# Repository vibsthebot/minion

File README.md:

# Minion - The Swiss Army Knife of Electronics

I'm a mac user, and i love my apple wired headphones.
mN phone doesn't have headphone jack and my computer doesn't have micro sd or usb a.
What if i made a dongle to rule all dongles, but added a potentiometer for step tracking and display + buttons to play games? And thats how I made Minion.

## Features

- USB hub with usb c input, usb a and microsd output
- TRRS jack for headphones
- Bourns Rotary Encoder
- Built-in display (SSD1351)
- Tactile buttons for user input
- Robust case design with custom rotary encoder cover and button extensions

## [Onshape](https://cad.onshape.com/documents/3528835cd7c24f4fa682b200/w/cef528dd0bdfad9cc29e4192/e/ba726118fc6deb21c1d0aa06?renderMode=0&uiState=683c8a64ca486b08201f4fa6)

## Images

### Schematic

### PCB Layout

### 3D Model of PCB

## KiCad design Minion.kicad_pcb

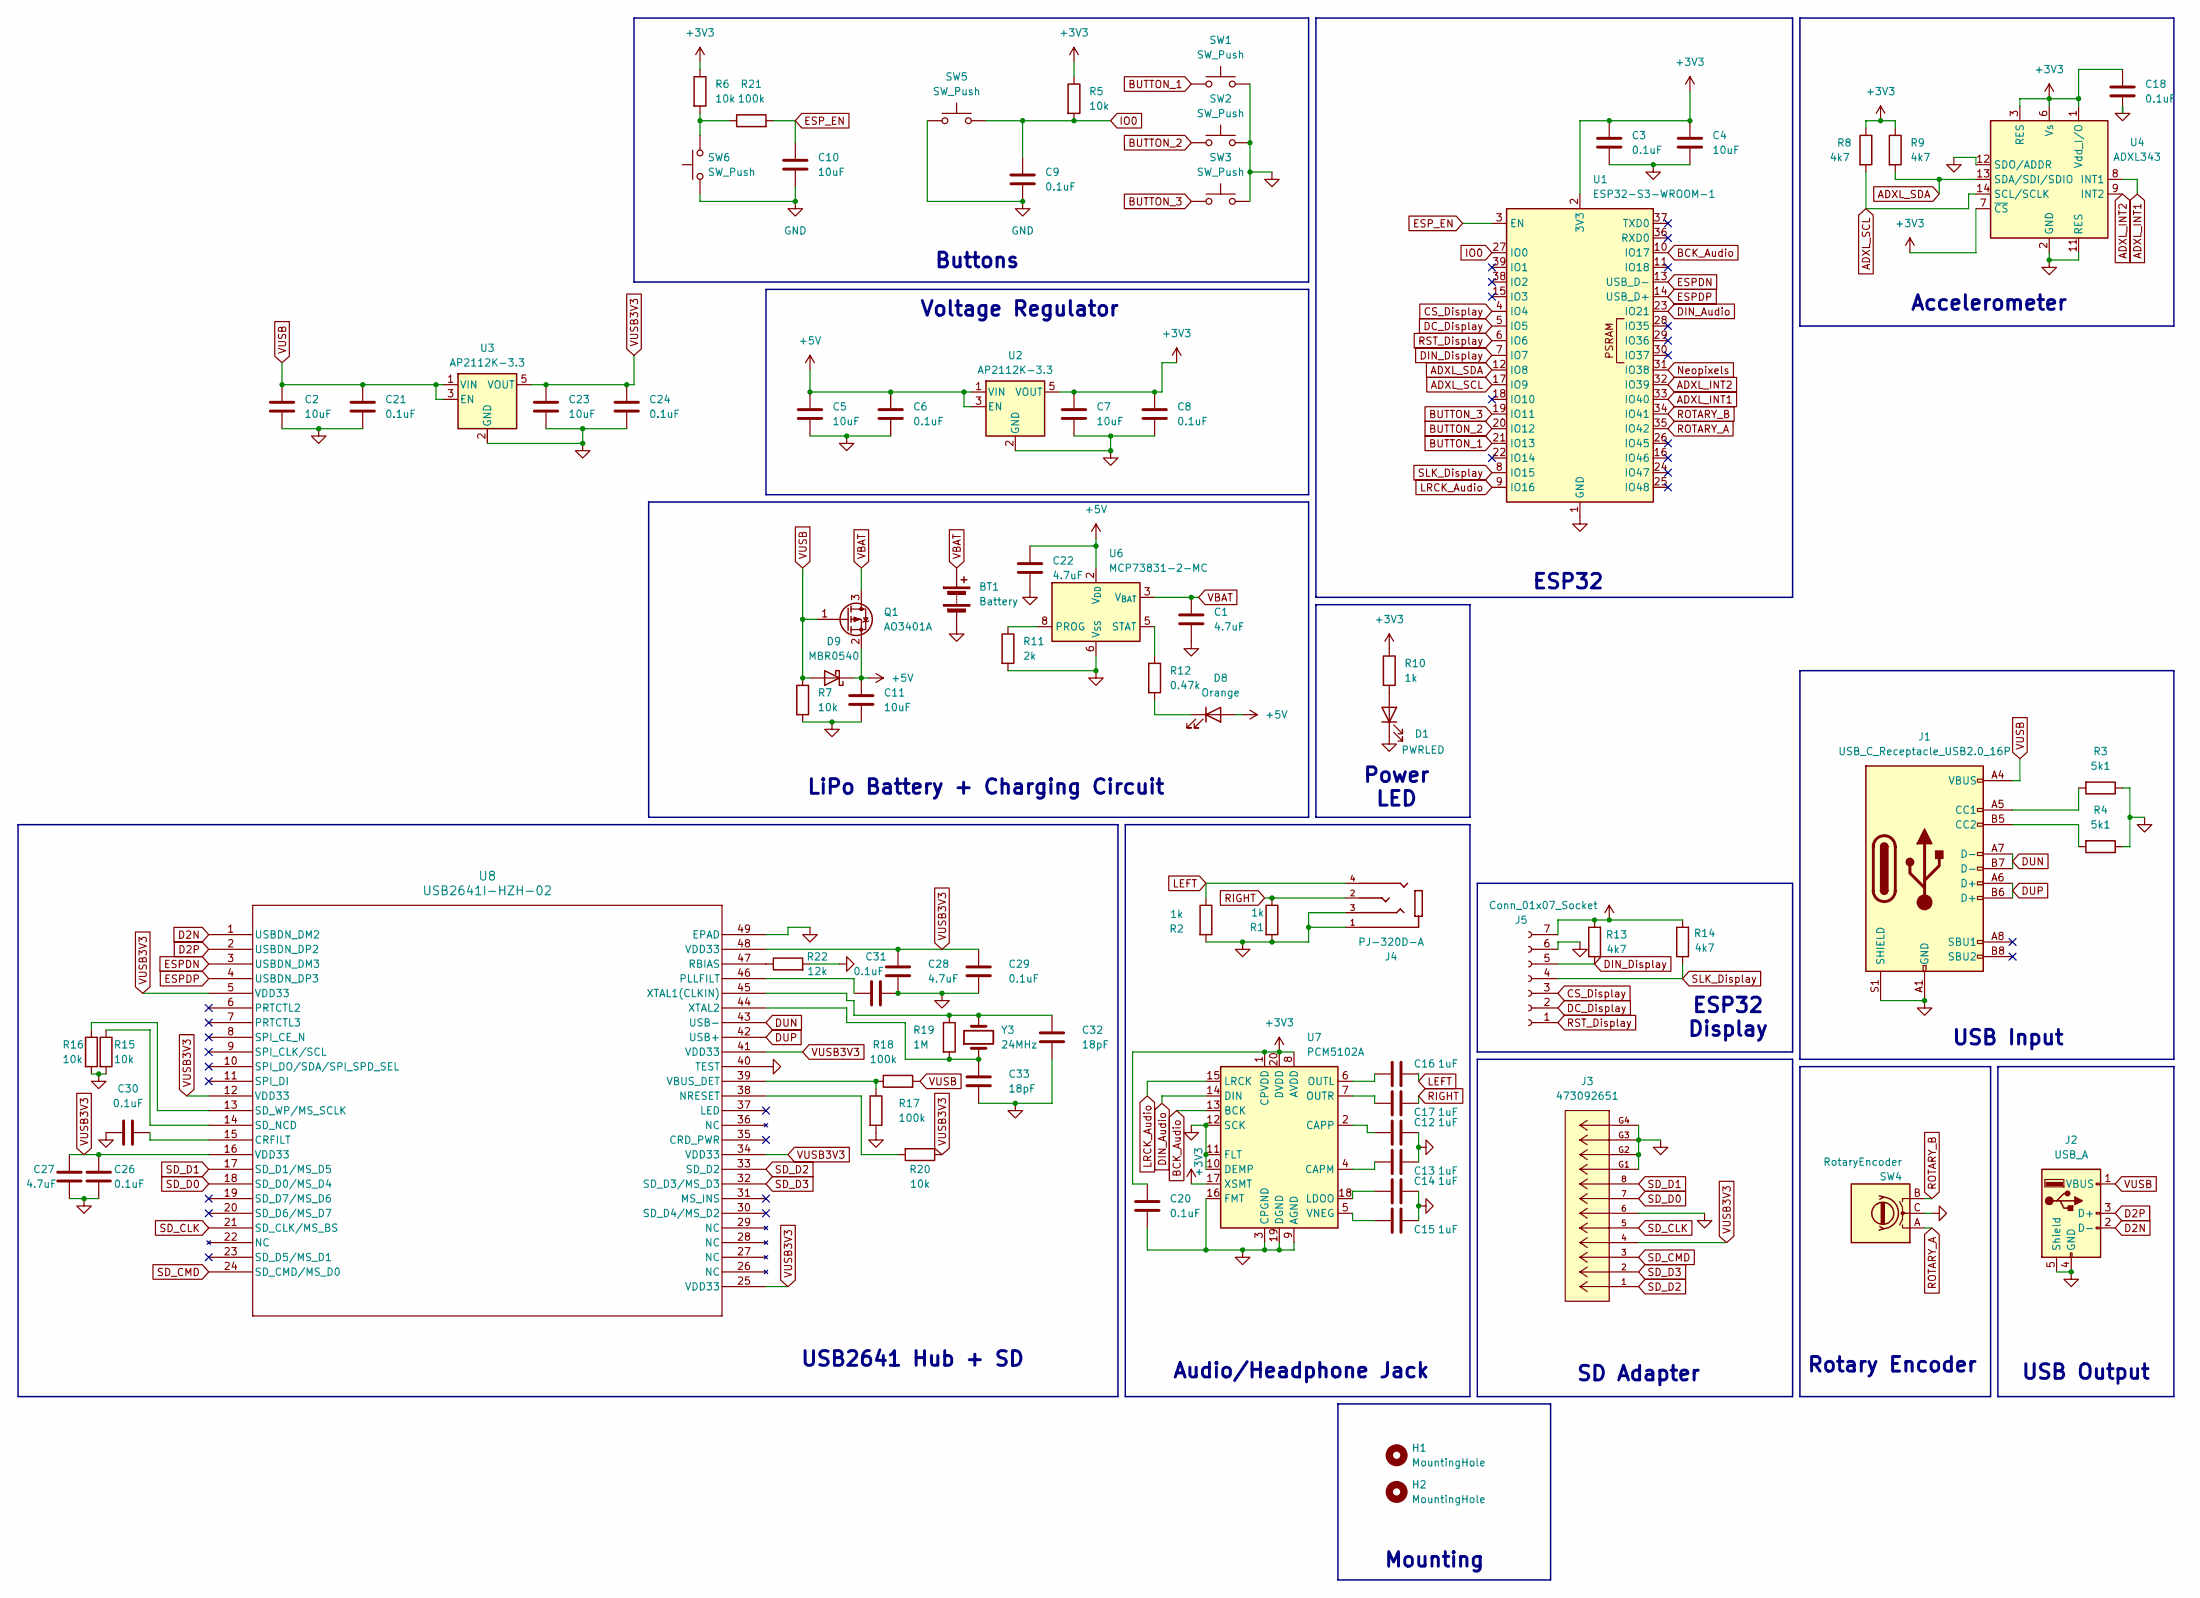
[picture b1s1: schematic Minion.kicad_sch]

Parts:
BT1: Battery; JST_PH_S2B-PH-K_1x02_P2.00mm_Horizontal; LCSC C265016
C1, C22, C27, C28: 4.7uF; C_0805_2012Metric; LCSC C1779
C2, C4, C5, C7, C10, C11, C23: 10uF; C_0805_2012Metric; LCSC C15850
C3, C6, C8, C9, C18, C20, C21, C24, C26, C29, C30, C31: 0.1uF; C_0805_2012Metric; LCSC C28233
C12, C13, C14, C15, C16, C17: 1uF; C_0805_2012Metric; LCSC C28323
C32, C33: 18pF; C_0402_1005Metric; LCSC C1549
D1: PWRLED; LED_0805_2012Metric; LCSC C84256
D8: Orange; LED_0805_2012Metric; LCSC C434437
D9: MBR0540; D_SOD-123; LCSC C77337
H1, H2: MountingHole; MountingHole_2.2mm_M2
J1: USB_C_Receptacle_USB2.0_16P; USB_C_Receptacle_HCTL_HC-TYPE-C-16P-01A; DigiKey 900-2171790001CT-ND
J2: USB_A; USB_A_Molex_67643_Horizontal; LCSC C464564
J3: 473092651; CONN12_47309-2651_MOL; MANUFACTURER_PART_NUMBER 473092651; DigiKey WM6700CT-ND
J4: PJ-320D-A; HRO_PJ-320D-A; PARTREV B; LCSC C95562
J5: Conn_01x07_Socket; SSD_1351; LCSC C124418
Q1: AO3401A; SOT-23; LCSC C306862
R1, R2, R10: 1k; R_0805_2012Metric; LCSC C17513
R3, R4: 5k1; R_0805_2012Metric; LCSC C27834
R5, R6, R7, R15, R16, R20: 10k; R_0805_2012Metric; LCSC C17414
R8, R9, R13, R14: 4k7; R_0805_2012Metric; LCSC C17673
R11: 2k; R_0805_2012Metric; LCSC C17604
R12: 0.47k; R_0805_2012Metric; LCSC C17710
R17, R18, R21: 100k; R_0805_2012Metric; LCSC C149504
R19: 1M; R_0805_2012Metric; LCSC C17514
R22: 12k; R_0805_2012Metric; LCSC C17444
SW1, SW2, SW3: SW_Push; SW_Push_1P1T_NO_6x6mm_H9.5mm; LCSC C455110
SW4: RotaryEncoder; RotaryEncoder_Bourns_Vertical_PEC12R-3x17F-Nxxxx; LCSC C18164805
SW5, SW6: SW_Push; SW_Push_1P1T_NO_CK_KMR2; LCSC C221676
U1: ESP32-S3-WROOM-1; LCSC C2913204
U2, U3: AP2112K-3.3; SOT-23-5; LCSC C51118
U4: ADXL343; LGA-14_3x5mm_P0.8mm_LayoutBorder1x6y; DigiKey 505-ADXL343BCCZ-ND
U6: MCP73831-2-MC; DFN-8-1EP_3x2mm_P0.5mm_EP1.7x1.4mm; LCSC C150772
U7: PCM5102A; TSSOP-20_4.4x6.5mm_P0.65mm; DigiKey 296-36707-1-ND
U8: USB2641I-HZH-02; QFN48_7X7MC_MCH; LCSC C633597
Y3: 24MHz; Crystal_SMD_5032-2Pin_5.0x3.2mm; LCSC C122520

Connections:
+3V3: C3.1, C4.1, C7.1, C8.1, C18.1, C20.1, J5.7, R5.1, R6.1, R8.1, R9.1, R10.1, R13.2, R14.2, U1.2 (3V3), U2.5 (VOUT), U4.1 (Vdd_I/O), U4.3 (RES), U4.6 (Vs), U4.7 (~CS), U7.1 (CPVDD), U7.8 (AVDD), U7.17 (XSMT), U7.20 (DVDD)
+5V: C5.1, C6.1, C11.1, C22.1, D8.2 (A), D9.1 (K), Q1.2 (S), U2.1 (VIN), U2.3 (EN), U6.1 (V_{DD}), U6.2 (V_{DD})
ADXL_INT1: U1.33 (IO40), U4.8 (INT1)
ADXL_INT2: U1.32 (IO39), U4.9 (INT2)
ADXL_SCL: R8.2, U1.17 (IO9), U4.14 (SCL/SCLK)
ADXL_SDA: R9.2, U1.12 (IO8), U4.13 (SDA/SDI/SDIO)
BCK_Audio: U1.10 (IO17), U7.13 (BCK)
BUTTON_1: SW1.1, U1.21 (IO13)
BUTTON_2: SW2.1, U1.20 (IO12)
BUTTON_3: SW3.1, U1.19 (IO11)
CS_Display: J5.3, U1.4 (IO4)
D2N: J2.2 (D-), U8.1 (USBDN_DM2)
D2P: J2.3 (D+), U8.2 (USBDN_DP2)
DC_Display: J5.2, U1.5 (IO5)
DIN_Audio: U1.23 (IO21), U7.14 (DIN)
DIN_Display: J5.5, R13.1, U1.7 (IO7)
DUN: J1.A7 (D-), J1.B7 (D-), U8.43 (USB-)
DUP: J1.A6 (D+), J1.B6 (D+), U8.42 (USB+)
ESPDN: U1.13 (USB_D-), U8.3 (USBDN_DM3)
ESPDP: U1.14 (USB_D+), U8.4 (USBDN_DP3)
ESP_EN: C10.1, R21.2, U1.3 (EN)
GND: BT1.2 (-), C1.2, C2.2, C3.2, C4.2, C5.2, C6.2, C7.2, C8.2, C9.2, C10.2, C11.2, C12.2, C13.2, C14.2, C15.2, C18.2, C20.2, C21.2, C22.2, C23.2, C24.2, C26.2, C27.2, C28.2, C29.2, C30.1, C31.2, C32.2, C33.2, D1.1 (K), J1.A1 (GND), J1.A12 (GND), J1.B1 (GND), J1.B12 (GND), J1.S1 (SHIELD), J2.4 (GND), J2.5 (Shield), J3.6, J3.G1, J3.G2, J3.G3, J3.G4, J4.1, J4.3, J5.6, R1.2, R2.2, R3.1, R4.1, R7.2, R11.2, R15.2, R16.2, R17.2, R22.2, SW1.2, SW2.2, SW3.2, SW4.C, SW5.1, SW6.1, U1.1 (GND), U1.40 (GND), U1.41 (GND), U2.2 (GND), U3.2 (GND), U4.2 (GND), U4.4 (GND), U4.5 (GND), U4.11 (RES), U4.12 (SDO/ADDR), U6.6 (V_{SS}), U7.3 (CPGND), U7.9 (AGND), U7.10 (DEMP), U7.11 (FLT), U7.12 (SCK), U7.16 (FMT), U7.19 (DGND), U8.40 (TEST), U8.49 (EPAD)
IO0: C9.1, R5.2, SW5.2, U1.27 (IO0)
LEFT: C16.2, J4.4, R2.1
LRCK_Audio: U1.9 (IO16), U7.15 (LRCK)
Neopixels: U1.31 (IO38)
unnamed: D1.2 (A), R10.2
unnamed: D8.1 (K), R12.2
unnamed: J1.A5 (CC1), R3.2
unnamed: J1.B5 (CC2), R4.2
unnamed: R6.2, R21.1, SW6.2
unnamed: R11.1, U6.8 (PROG)
unnamed: R12.1, U6.5 (STAT)
unnamed: C13.1, U7.4 (CAPM)
unnamed: C12.1, U7.2 (CAPP)
unnamed: C14.1, U7.18 (LDOO)
unnamed: C16.1, U7.6 (OUTL)
unnamed: C17.1, U7.7 (OUTR)
unnamed: C15.1, U7.5 (VNEG)
unnamed: C30.2, U8.15 (CRFILT)
unnamed: R20.2, U8.38 (NRESET)
unnamed: C31.1, U8.46 (PLLFILT)
unnamed: R22.1, U8.47 (RBIAS)
unnamed: R15.1, U8.14 (SD_NCD)
unnamed: R16.1, U8.13 (SD_WP/MS_SCLK)
unnamed: R17.1, R18.1, U8.39 (VBUS_DET)
unnamed: C32.1, R19.1, U8.45 (XTAL1(CLKIN)), Y3.2
unnamed: C33.1, R19.2, U8.44 (XTAL2), Y3.1
RIGHT: C17.2, J4.2, R1.1
ROTARY_A: SW4.A, U1.35 (IO42)
ROTARY_B: SW4.B, U1.34 (IO41)
RST_Display: J5.1, U1.6 (IO6)
SD_CLK: J3.5, U8.21 (SD_CLK/MS_BS)
SD_CMD: J3.3, U8.24 (SD_CMD/MS_D0)
SD_D0: J3.7, U8.18 (SD_D0/MS_D4)
SD_D1: J3.8, U8.17 (SD_D1/MS_D5)
SD_D2: J3.1, U8.33 (SD_D2)
SD_D3: J3.2, U8.32 (SD_D3/MS_D3)
SLK_Display: J5.4, R14.1, U1.8 (IO15)
VBAT: BT1.1 (+), C1.1, Q1.3 (D), U6.3 (V_{BAT}), U6.4 (V_{BAT})
VUSB: C2.1, C21.1, D9.2 (A), J1.A4 (VBUS), J1.A9 (VBUS), J1.B4 (VBUS), J1.B9 (VBUS), J2.1 (VBUS), Q1.1 (G), R7.1, R18.2, U3.1 (VIN), U3.3 (EN)
VUSB3V3: C23.1, C24.1, C26.1, C27.1, C28.1, C29.1, J3.4, R20.1, U3.5 (VOUT), U8.5 (VDD33), U8.12 (VDD33), U8.16 (VDD33), U8.25 (VDD33), U8.34 (VDD33), U8.41 (VDD33), U8.48 (VDD33)

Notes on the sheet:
Voltage Regulator
Buttons
Audio/Headphone Jack
ESP32
Power LED
Mounting
USB2641 Hub + SD
Accelerometer
LiPo Battery + Charging Circuit
USB Input
USB Output
Rotary Encoder
SD Adapter
ESP32 Display

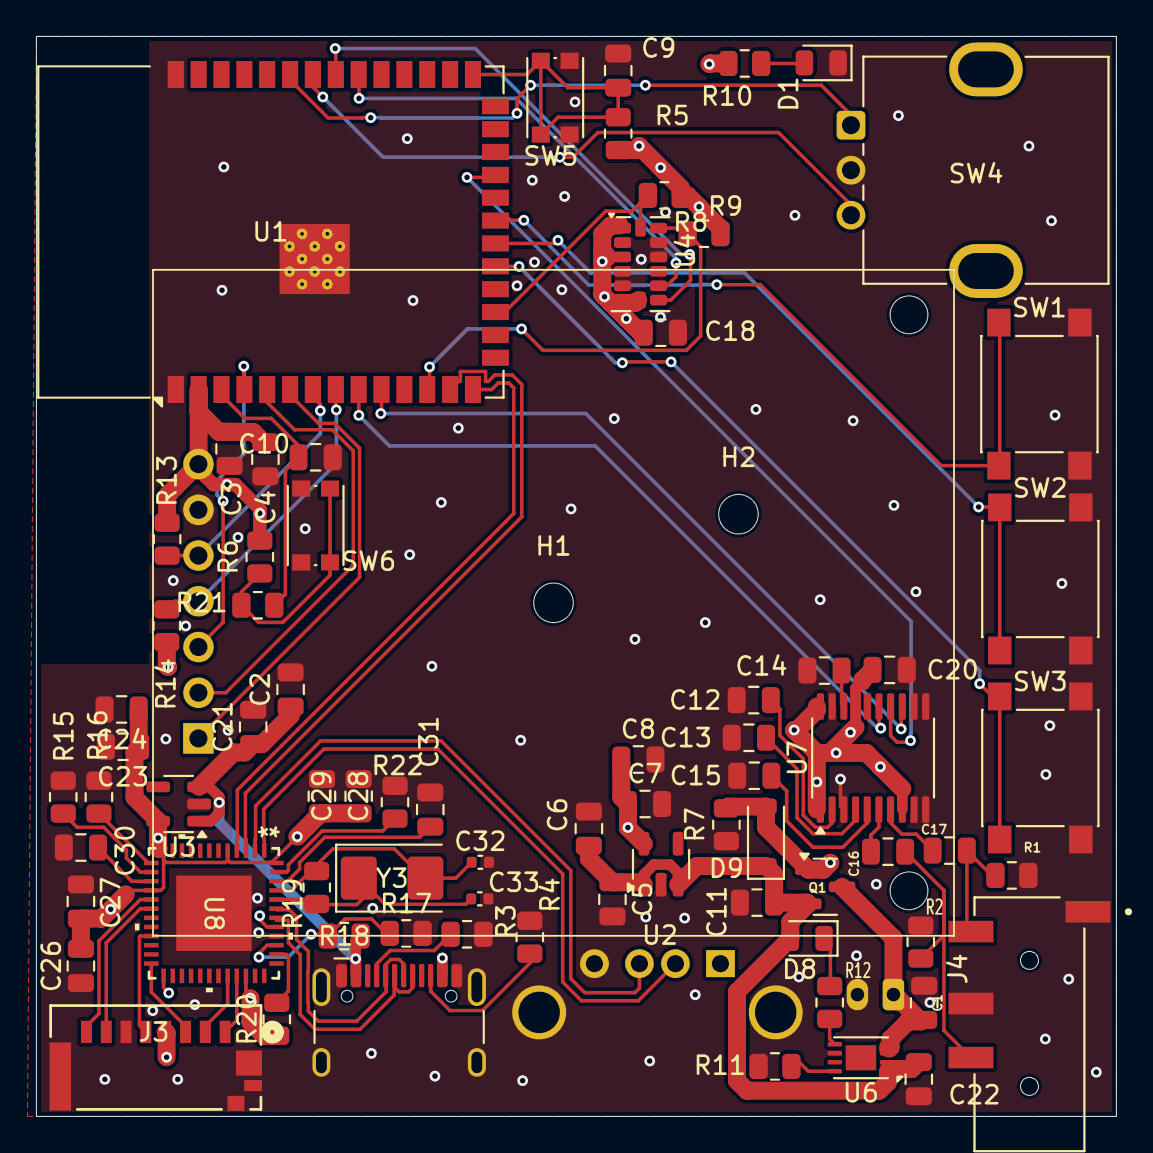
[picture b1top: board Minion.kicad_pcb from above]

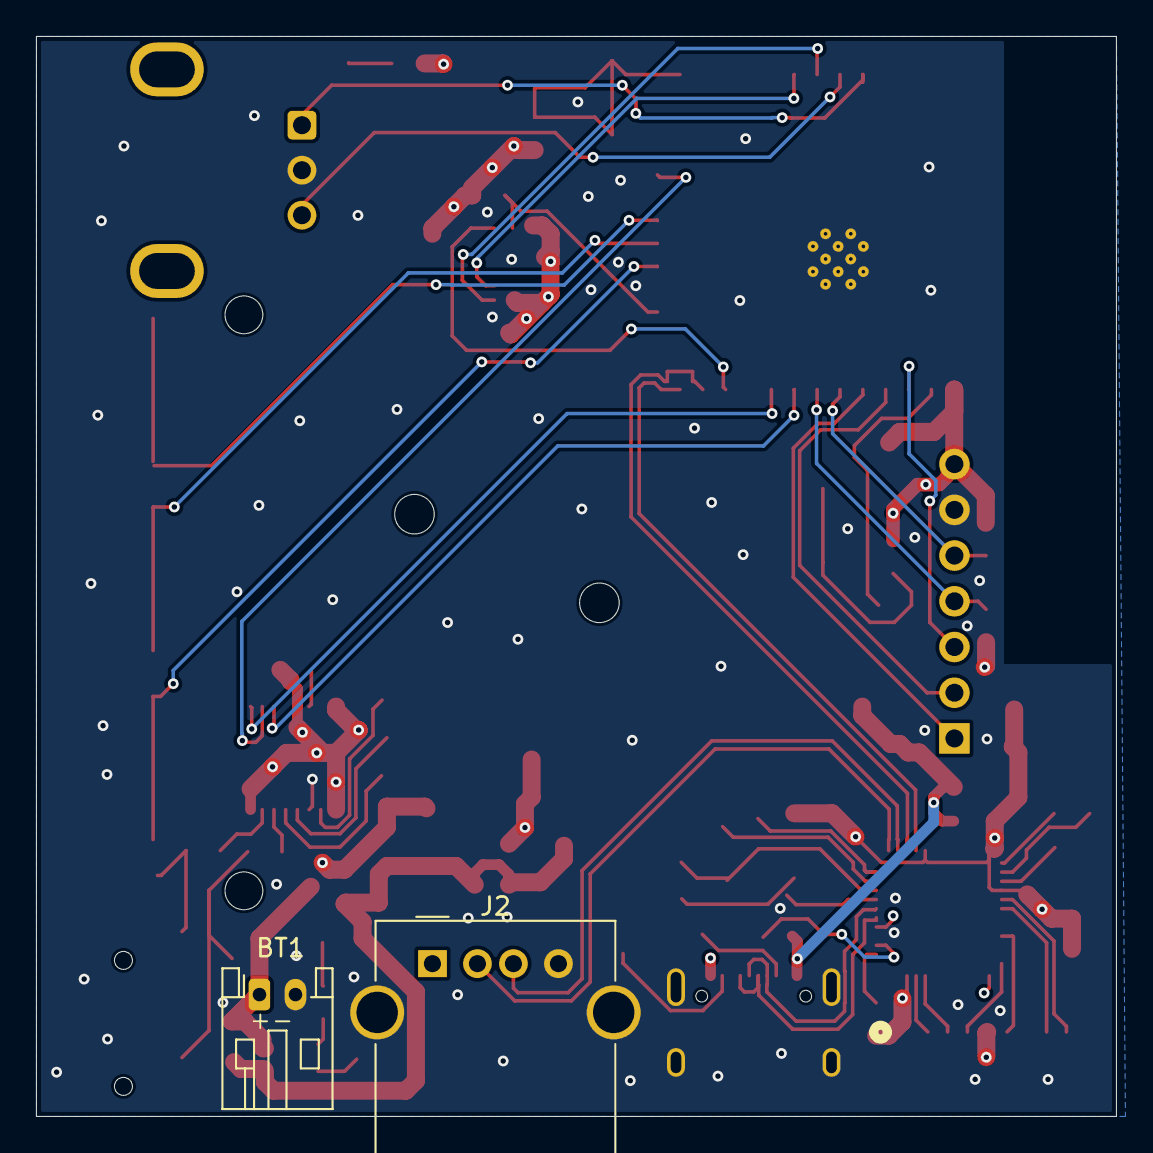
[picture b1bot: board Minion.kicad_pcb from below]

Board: 4 copper layers, 60.0 x 60.0 mm, 79 parts (2 on the bottom side), 61 nets.

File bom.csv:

Qty,Item,LCSC/DigiKey Min Quantity,Individual Price,What the price should be,What the price really is,Price for 2 boards,LCSC Part Number,DigiKey Part Number,Link/Notes
1,Battery,10,0.0621,0.0621,0.621,0.62,C265016,,
5,10uF,50,0.012,0.06,0.6,0.6,C40894,,
7,1uF,25,0.0034,0.0238,0.085,0.09,C215803,,
5,0.1uF,20,0.0097,0.0485,0.194,0.19,C476766,,
1,PWRLED,50,0.013,0.013,0.65,0.65,C84256,,
4,WS2812B,5,0.0835,0.334,0.4175,0.84,C114586,,
1,S-LMBR340FT1G,10,0.0249,0.0249,0.249,0.25,C2972823,,
1,Orange,50,0.0088,0.0088,0.44,0.44,C434437,,
1,MBR0540,20,0.0313,0.0313,0.626,0.63,C77337,,
1,Conn_01x07_Socket,5,0.1469,0.1469,0.7345,0.73,C124418,,
1,USB_C_Receptacle_USB2.0_16P,1,0.83,0.83,0.83,1.66,,900-2171790001CT-ND,
1,USB_A,1,0.5764,0.5764,0.5764,1.15,,,
1,473092651,1,1.94,1.94,1.94,3.88,C464564,WM6700CT-ND,
1,PJ-320D-A,5,0.0972,0.0972,0.486,0.49,,,
1,AO3401A,20,0.0521,0.0521,1.042,1.04,C95562,,
3,1k,100,0.0019,0.0057,0.19,0.19,C306862,,
2,5.1k,100,0.0019,0.0038,0.19,0.19,C95781,,
2,10k,100,0.0012,0.0024,0.12,0.12,C27834,,
1,2.7k,100,0.0013,0.0013,0.13,0.13,C2930231,,
6,4.7k,100,0.0022,0.0132,0.22,0.22,C2907305,,
3,SW_Push,10,0.0427,0.1281,0.427,0.43,C60816,,
1,RotaryEncoder,1,2.3596,2.3596,2.3596,4.72,C455110,,
2,SW_Push,1,0.4706,0.9412,0.9412,1.88,C18164805,,
1,ESP32-S3-WROOM-1,1,5.8792,5.8792,5.8792,11.76,C221676,,
1,AMS1117-3.3,1,0.68,0.68,0.68,1.36,C2913204,4518-AMS1117-3.3CT-ND,
1,FE1.1s,1,0.6214,0.6214,0.6214,1.24,,,
1,ADXL343,1,3.35,3.35,3.35,6.7,C9359,505-ADXL343BCCZ-ND,
1,CH376T,1,3.6696,3.6696,3.6696,7.34,,,
1,MCP73831-2-MC,1,1.2194,1.2194,1.2194,2.44,C21282,,
1,PCM5102A,1,4.43,4.43,4.43,8.86,C150772,296-36707-1-ND,
2,12MHz,5,0.1676,0.3352,0.838,0.84,,,
1,SSD1351,1,19.55,19.55,19.55,19.55,C3035202,,
1,Stencils + PCB,1,16,16,16,16,,,https://www.aliexpress.us/item/2255799949791867.html
1,JLCCNC Machined case,1,61.87,61.87,61.87,61.87,,,"optional, may get manufactured in house"
1,DigiKey Shipping,1,8,8,8,8,,,
1,LCSC + JLC shipping,1,20,20,20,20,,,
,,,152.2099,153.3091,160.1768,187.1,,,

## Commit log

2025-05-02 created project
2025-05-15 finished most of pcb, added 3d models
2025-05-16 Updated journal for yesterday
2025-05-21 finished pcb and updated journal
2025-05-29 updated journal and readme
2025-06-01 added bom with prices
2025-06-01 fixed bom with shipping
2025-06-12 Updated from feedback
2025-06-20 Finished PCB!
